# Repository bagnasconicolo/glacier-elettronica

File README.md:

# glacier-elettronica — Rivelatore di raggi cosmici

Front-end di lettura per un **rivelatore di muoni cosmici** basato su SiPM +
scintillatore: amplificatore veloce, discriminatore a soglia regolabile,
generazione del bias del SiPM, uscita TTL e **uscita 3,3 V per Raspberry Pi**.

Ricostruzione completa in KiCad — dal solo PDF scansionato dello schema originale
INFN sez. Torino ("Riv. Cosmici 2024 — Amplif, alim, soglie", S. Gallian) —
accompagnata da simulazioni circuitali non lineari, un verificatore che gira
**direttamente dallo schema**, la **simulazione LTspice della scheda completa** e un
sito didattico interattivo.

## Come funziona il circuito

Un muone attraversa lo scintillatore e produce un lampo di luce; il **SiPM**
(AFBR-S4N22P014M, polarizzato a ~38,4 V generati a bordo) lo converte in un
impulso di corrente. Due transistor — **BFR93A** (Q1) e **MMBTH81** (Q2) —
amplificano di ~28×. Il comparatore **MAX961** confronta con la soglia impostata
dal trimmer V2 e produce l'impulso digitale **CMP_Q**; una rete C9/R16 (latch)
evita i doppi conteggi. Da qui il segnale va al driver **MCP1402** (uscita TTL su
J2) e al buffer **74LVC1G17** alimentato a 3,3 V, che lo porta sul connettore
LEMO/J4 a 0–3,3 V, pronto per un GPIO del **Raspberry Pi**. Un timer **555** accende un LED per
11 ms a ogni evento.

Rate reale su una paletta 10×10 cm a livello del mare: **~1,7 muoni/s**.

| Schema | PCB |
|---|---|
|  |  |

## Struttura del repository

```
hardware/          progetto KiCad (schema, PCB, librerie, Gerber, BOM)
  riv_cosmici.kicad_pro/.kicad_sch/.kicad_pcb
  riv.kicad_sym, rivlib.pretty/        librerie simboli e footprint del progetto
  gerber/, riv_cosmici_gerber.zip      Gerber RS-274X + Excellon (pronti per il fab)
  bom/                                 distinta base (.xlsx e .csv) con codici Farnell/RS
  PRIMA_DI_ORDINARE.md                 cosa e' verificato e cosa decidere prima dell'ordine
  jlcpcb/                              Gerber, BOM e CPL per PCB + montaggio su JLCPCB
  variante_3ch/                        VARIANTE A 3 CANALI + coincidenza AND, uscite LEMO
  alpha_bpw21/                         mini-rivelatore di ALPHA con fotodiodo BPW21 (1 op-amp + Arduino)
  render3d/                            render 3D delle schede montate (three.js)
  previews/                            anteprime PNG
  generator/                           script Python che GENERANO lo hardware (sorgente)
simulation/        modelli circuitali non lineari + verifica dallo schema
  ltspice/             SCHEDA COMPLETA per LTspice (.asc) e ngspice (.cir) + verifica
  sim_catena.py        catena di segnale (SiPM -> ampli -> comparatore)
  sim_muoni.py         treno di muoni (Poisson + Landau) + dark count
  sim_buffer.py        (variante superata) vecchio buffer a 2 transistor
  sim_treno_completo.py (variante superata) catena fino a un Arduino a 5 V
  netlist_from_kicad.py   estrae la netlist dal .kicad_sch
  verify_from_schematic.py simula DALLA netlist estratta (front-end + uscita)
  make_recap.py        genera il PDF di recap
  riv_cosmici_frontend.cir  netlist SPICE del solo front-end (storica)
  figures/             grafici generati
web/               sito didattico interattivo (single-file, offline)
firmware/          (variante superata) sketch Arduino
docs/              schemi in PDF (1 e 3 canali), RECAP_progetto.pdf, schema_originale_INFN.pdf
```

## Due versioni

| | Scheda a 1 canale | Variante a 3 canali |
|---|---|---|
| Dove | `hardware/` | `hardware/variante_3ch/` |
| Barre / SiPM | 1 | 3 (bias e soglia regolabili per canale) |
| Uscite | LEMO/header 3,3 V + TTL 5 V | 3 LEMO 00 (canali) + 1 LEMO 00 (AND) |
| Coincidenza | — | 74LVC1G11 con jumper di esclusione |
| Test point | — | 6 per canale + 6 comuni |
| PCB | 80 × 55 mm | 103 × 215 mm, serigrafia didattica, 8 fori M3 |
| Schema PDF | `docs/schema_riv_cosmici_1canale.pdf` | `docs/schema_riv_cosmici_3canali.pdf` |

Render 3D delle schede montate: `hardware/render3d/out/1ch/` e `out/3ch/`
(rigenerabili con `python scene.py 3ch && node shoot.mjs 3ch`).

## Hardware (KiCad)

Apri `hardware/riv_cosmici.kicad_pro` con **KiCad 6 o successivo**. Le librerie di
progetto (`riv.kicad_sym`, `rivlib.pretty`) sono già referenziate da `sym-lib-table`
e `fp-lib-table` con percorso `${KIPRJMOD}`. I Gerber in `hardware/gerber/` sono
pronti per la produzione (2 layer, 80×55 mm; DRC geometrico e connettività a zero
errori). La BOM in `hardware/bom/` riporta i codici d'ordine Farnell/RS trascritti
dal progetto originale.

### Prima di ordinare

Leggi **[`hardware/PRIMA_DI_ORDINARE.md`](hardware/PRIMA_DI_ORDINARE.md)**: elenca cosa è
stato verificato (schema = originale INFN pin per pin, piedinature sui datasheet, DRC e
connettività del PCB, simulazione della scheda intera) e i punti da decidere al
montaggio, che non richiedono modifiche al PCB: R3 per restare sotto i 40 V del
LT3461, i condensatori d'uscita dei regolatori, l'ingombro di L1 e il LEMO.

Rigenerare tutto (schema, PCB, Gerber, BOM, anteprime) dal modello dati:

```bash
cd hardware/generator
python gen_sch.py && python gen_pcb.py && python gerber_out.py && python gen_bom.py
python gen_jlcpcb.py   # dopo aver aggiornato hardware/gerber e lo zip
python render_sch.py && python render_pcb.py
# schema, PCB e Gerber escono in generator/riv_cosmici/: copiarli in hardware/
```

## Simulazioni

Tutto in Python puro (nessun SPICE richiesto): un solver MNA + Newton con transistor
Ebers-Moll. Installa le dipendenze e lancia gli script da `simulation/`:

```bash
pip install -r requirements.txt
cd simulation
python sim_catena.py          # risposta della catena, punto di lavoro DC
python sim_muoni.py           # treno di muoni + dark count, reiezione
python sim_buffer.py          # buffer: CMP_Q vs TTL, storage time
python sim_treno_completo.py  # end-to-end fino al pin Arduino
```

Risultati principali (dettaglio in `simulation/RISULTATI_SIMULAZIONE.md`):
guadagno ~35 mV/fotoelettrone, saturazione oltre ~40 p.e.; soglia regolabile da
~2 mV a ~1,3 V; 7 muoni → 7 conteggi con 46 dark count rigettati; rate medio
1,68 conteggi/s a scala reale.

### Simulazione LTspice della scheda COMPLETA

In `simulation/ltspice/` c'è tutta la scheda — alimentazioni, boost 40 V, bias del SiPM,
front-end, soglia, comparatore con latch, driver TTL, 555 + LED, uscita per il
Raspberry Pi — come **schema LTspice** (`riv_cosmici_completo.asc`, si apre e si preme
Run) e come netlist (`.cir`, anche per ngspice). È generata dallo stesso modello dati
dello schema KiCad: riferimenti e nomi delle reti coincidono.

```bash
cd simulation/ltspice
python verifica_ltspice.py   # .asc == .cir, copertura KiCad, 21 controlli, grafico
```

Dettagli, parametri e limiti dei modelli: [`simulation/ltspice/LEGGIMI.md`](simulation/ltspice/LEGGIMI.md).

### Verifica DIRETTA dallo schema

Le simulazioni normali usano una netlist trascritta a mano. Per legare la verifica
allo schema vero:

```bash
cd simulation
python verify_from_schematic.py            # front-end letto dal .kicad_sch
python verify_from_schematic.py --uscita   # + stadio d'uscita (U9 -> J4) dal .kicad_sch
```

`netlist_from_kicad.py` estrae la netlist per geometria direttamente dal file
`hardware/riv_cosmici.kicad_sch` (valori, fili, etichette, alimentazioni) e
`verify_from_schematic.py` la simula: il punto di lavoro coincide col riferimento al
millivolt, e un errore introdotto nello schema (valore o cablaggio) cambia il
risultato — così la simulazione diventa una vera verifica dello schema.

Il **PDF di recap** con tutti i grafici e i numeri si rigenera con:
`python make_recap.py` → `docs/RECAP_progetto.pdf`.

## Sito didattico

In `web/` ci sono pagine HTML autonome (funzionano offline, senza librerie
esterne), con dentro lo **stesso solver circuitale** portato in JavaScript:

- `schematico_interattivo.html` — lo schema elettrico "vivo": lancia un muone al
  rallentatore, sonde sui nodi, componenti cliccabili, trimmer della soglia
  trascinabile, oscilloscopio.
- `viaggio_del_muone.html` — la catena stadio per stadio, con i grafici ricalcolati
  in tempo reale.
- `rivelatore_cosmici.html` — cruscotto con muoni animati e conteggio.

## Lettura con Raspberry Pi

J4 pin 1 → un GPIO (es. GPIO17) con 330 Ω in serie, J4 pin 2 → GND. L'uscita è
0–3,3 V. Ogni muone dà un impulso di ≥ 84 ns: va contato **a interrupt sul fronte di
salita** (es. `libgpiod`, eventi `RISING_EDGE`), non in polling. **Non collegare J2**
(TTL a 5 V) al Pi. Lo sketch in `firmware/` è della vecchia variante Arduino a 5 V.

## Rigenerare lo hardware

Gli script in `hardware/generator/` sono il "sorgente" da cui sono stati generati
schema, PCB, Gerber e BOM (via codice, per costruzione riproducibile), tutti dallo
stesso modello dati `netdata.py`; i comandi sono nella sezione "Prima di ordinare".
Anche la simulazione LTspice (`simulation/ltspice/gen_ltspice.py`) parte da lì.

## Crediti e licenza

Progetto originale: **INFN sezione di Torino**, "Riv. Cosmici 2024 — Amplif, alim,
soglie" (S. Gallian, 2024). Ricostruzione KiCad, buffer, simulazioni, verifica e
materiale didattico: questo repository.

Rilasciato sotto **CERN Open Hardware Licence Version 2 — Weakly Reciprocal**
(CERN-OHL-W-2.0): vedi `LICENSE` e `LICENSE.CERN-OHL-W-2.0.txt`. Il software di
supporto (script Python/JS, firmware) è distribuito con lo stesso spirito.

## Monitor delle tensioni (scheda a 3 canali)

Un ADC MCP3424 sulla scheda legge i tre bias dei SiPM e l'alta tensione; il Raspberry Pi li legge in I²C con `software/monitor_tensioni.py`. Dettagli e verifica che non disturbi le misure: `hardware/variante_3ch/LEGGIMI.md` e `simulation/ltspice/verifica_monitor.py`.

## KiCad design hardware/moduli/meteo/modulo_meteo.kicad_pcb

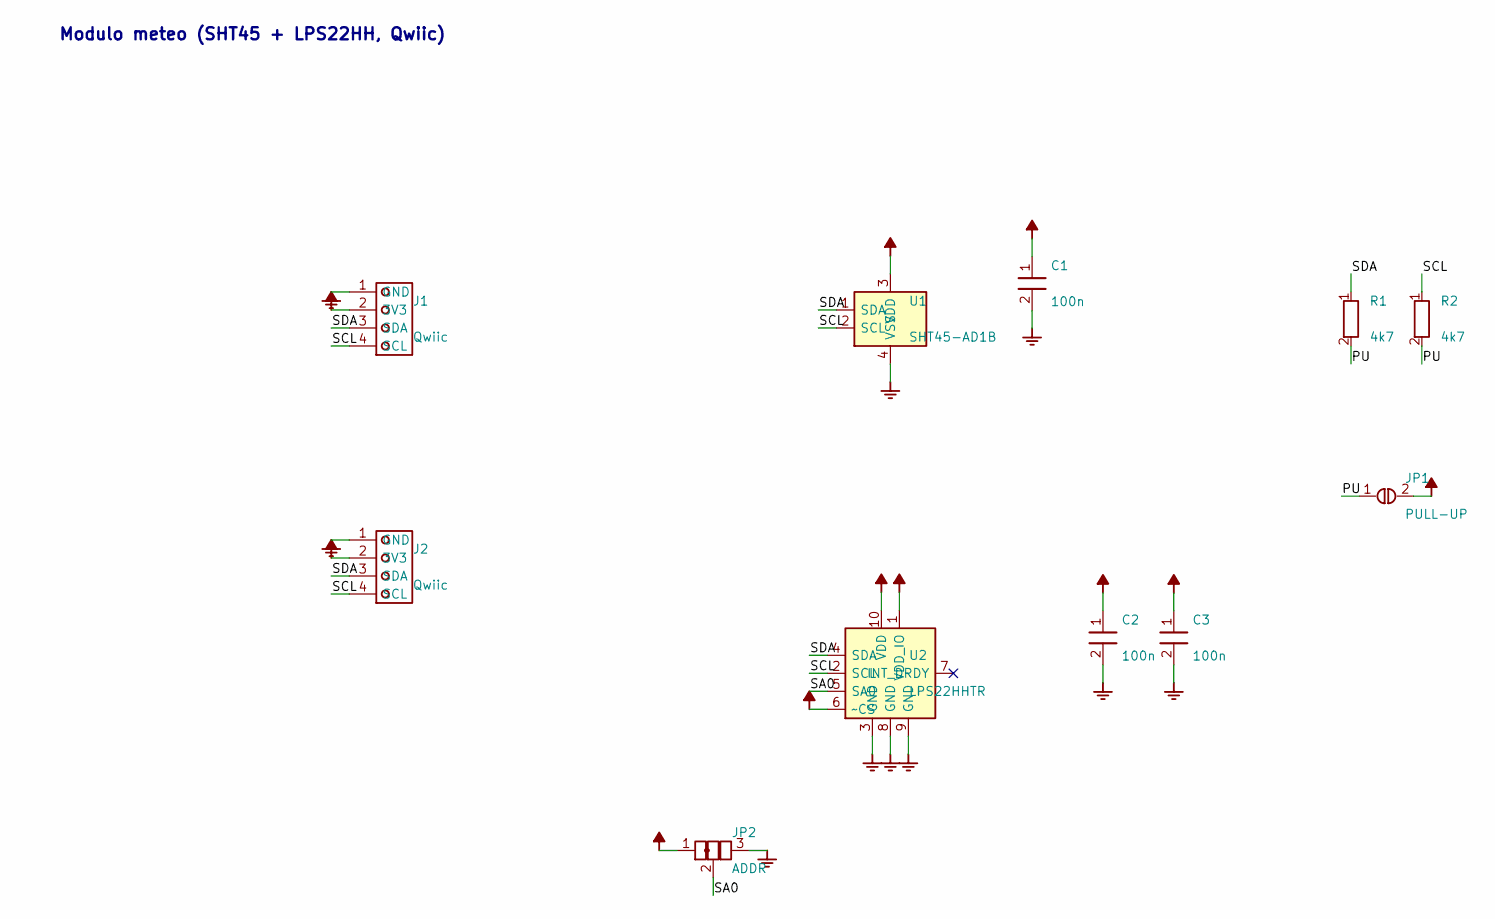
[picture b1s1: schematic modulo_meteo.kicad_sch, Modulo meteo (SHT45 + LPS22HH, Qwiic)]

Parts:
C1, C2, C3: 100n; C_0603_1608Metric
J1, J2: Qwiic; JST_SH_SM04B-SRSS-TB_1x04-1MP_P1.00mm_Horizontal
JP1: PULL-UP; SolderJumper-2_P1.3mm_Open_RoundedPad1.0x1.5mm
JP2: ADDR; SolderJumper-3_P1.3mm_Bridged12_RoundedPad1.0x1.5mm
R1, R2: 4k7; R_0603_1608Metric
U1: SHT45-AD1B; Sensirion_DFN-4_1.5x1.5mm_P0.8mm_SHT4x_KeepoutCentro
U2: LPS22HHTR; ST_HLGA-10_2x2mm_P0.5mm_LayoutBorder3x2y

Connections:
+3V3: C1.1, C2.1, C3.1, J1.2 (3V3), J2.2 (3V3), JP1.2, JP2.1, U1.3 (VDD), U2.1 (VDD_IO), U2.6 (~CS), U2.10 (VDD)
GND: C1.2, C2.2, C3.2, J1.1 (GND), J2.1 (GND), JP2.3, U1.4 (VSS), U2.3 (GND), U2.8 (GND), U2.9 (GND)
PU: JP1.1, R1.2, R2.2
SA0: JP2.2, U2.5 (SA0)
SCL: J1.4 (SCL), J2.4 (SCL), R2.1, U1.2 (SCL), U2.2 (SCL)
SDA: J1.3 (SDA), J2.3 (SDA), R1.1, U1.1 (SDA), U2.4 (SDA)

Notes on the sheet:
Modulo meteo (SHT45 + LPS22HH, Qwiic)

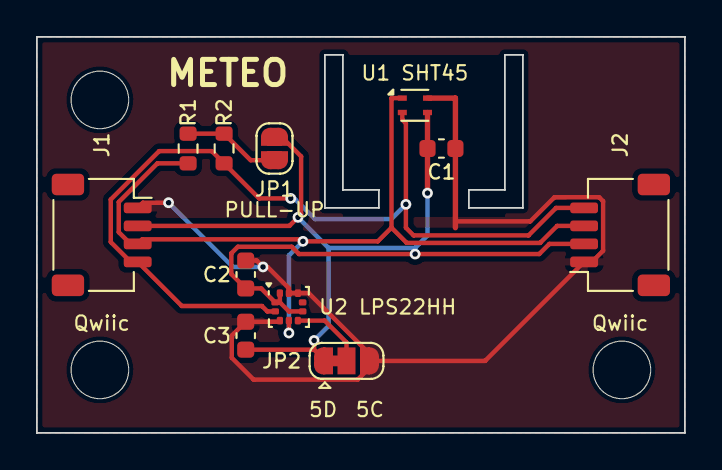
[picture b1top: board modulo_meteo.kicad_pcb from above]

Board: 2 copper layers, 36.0 x 22.0 mm, 14 parts (0 on the bottom side), 6 nets.

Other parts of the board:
H1, H2, H3: M3; MountingHole_3.2mm_M3

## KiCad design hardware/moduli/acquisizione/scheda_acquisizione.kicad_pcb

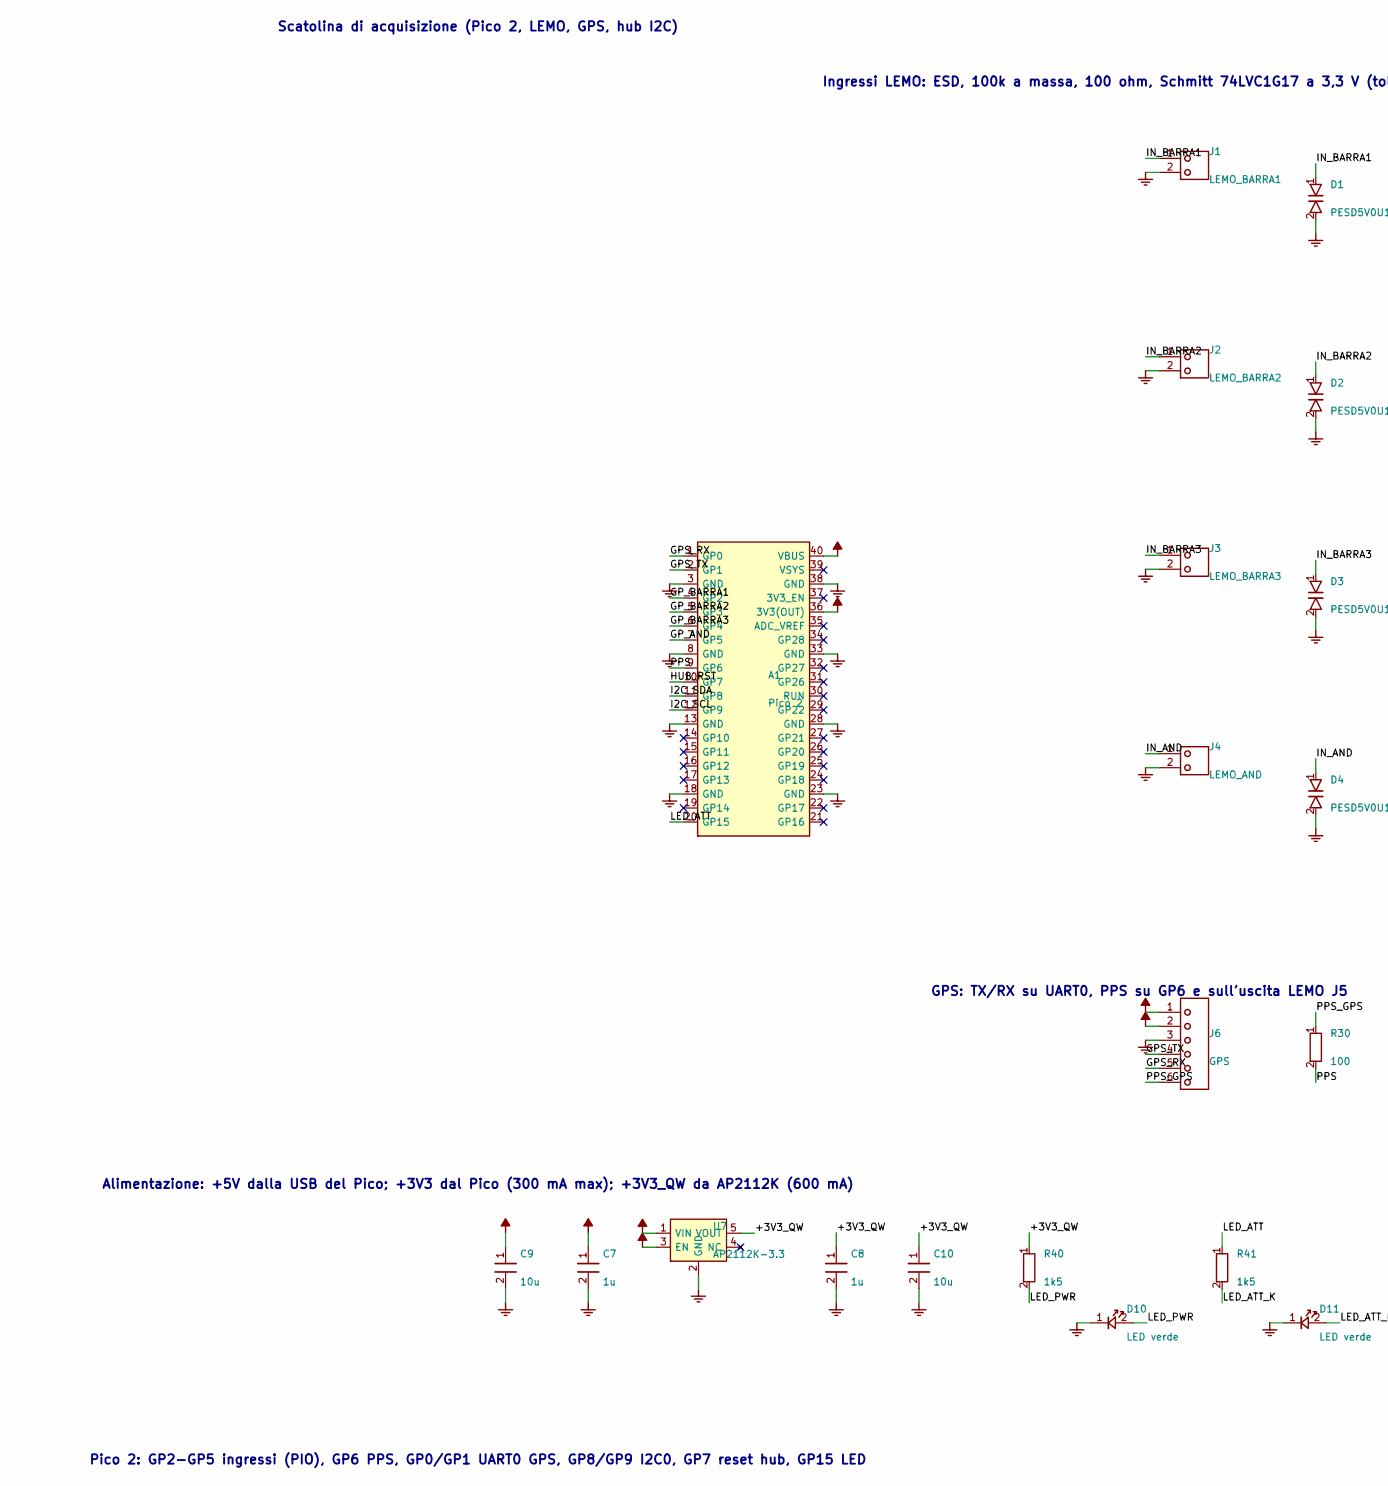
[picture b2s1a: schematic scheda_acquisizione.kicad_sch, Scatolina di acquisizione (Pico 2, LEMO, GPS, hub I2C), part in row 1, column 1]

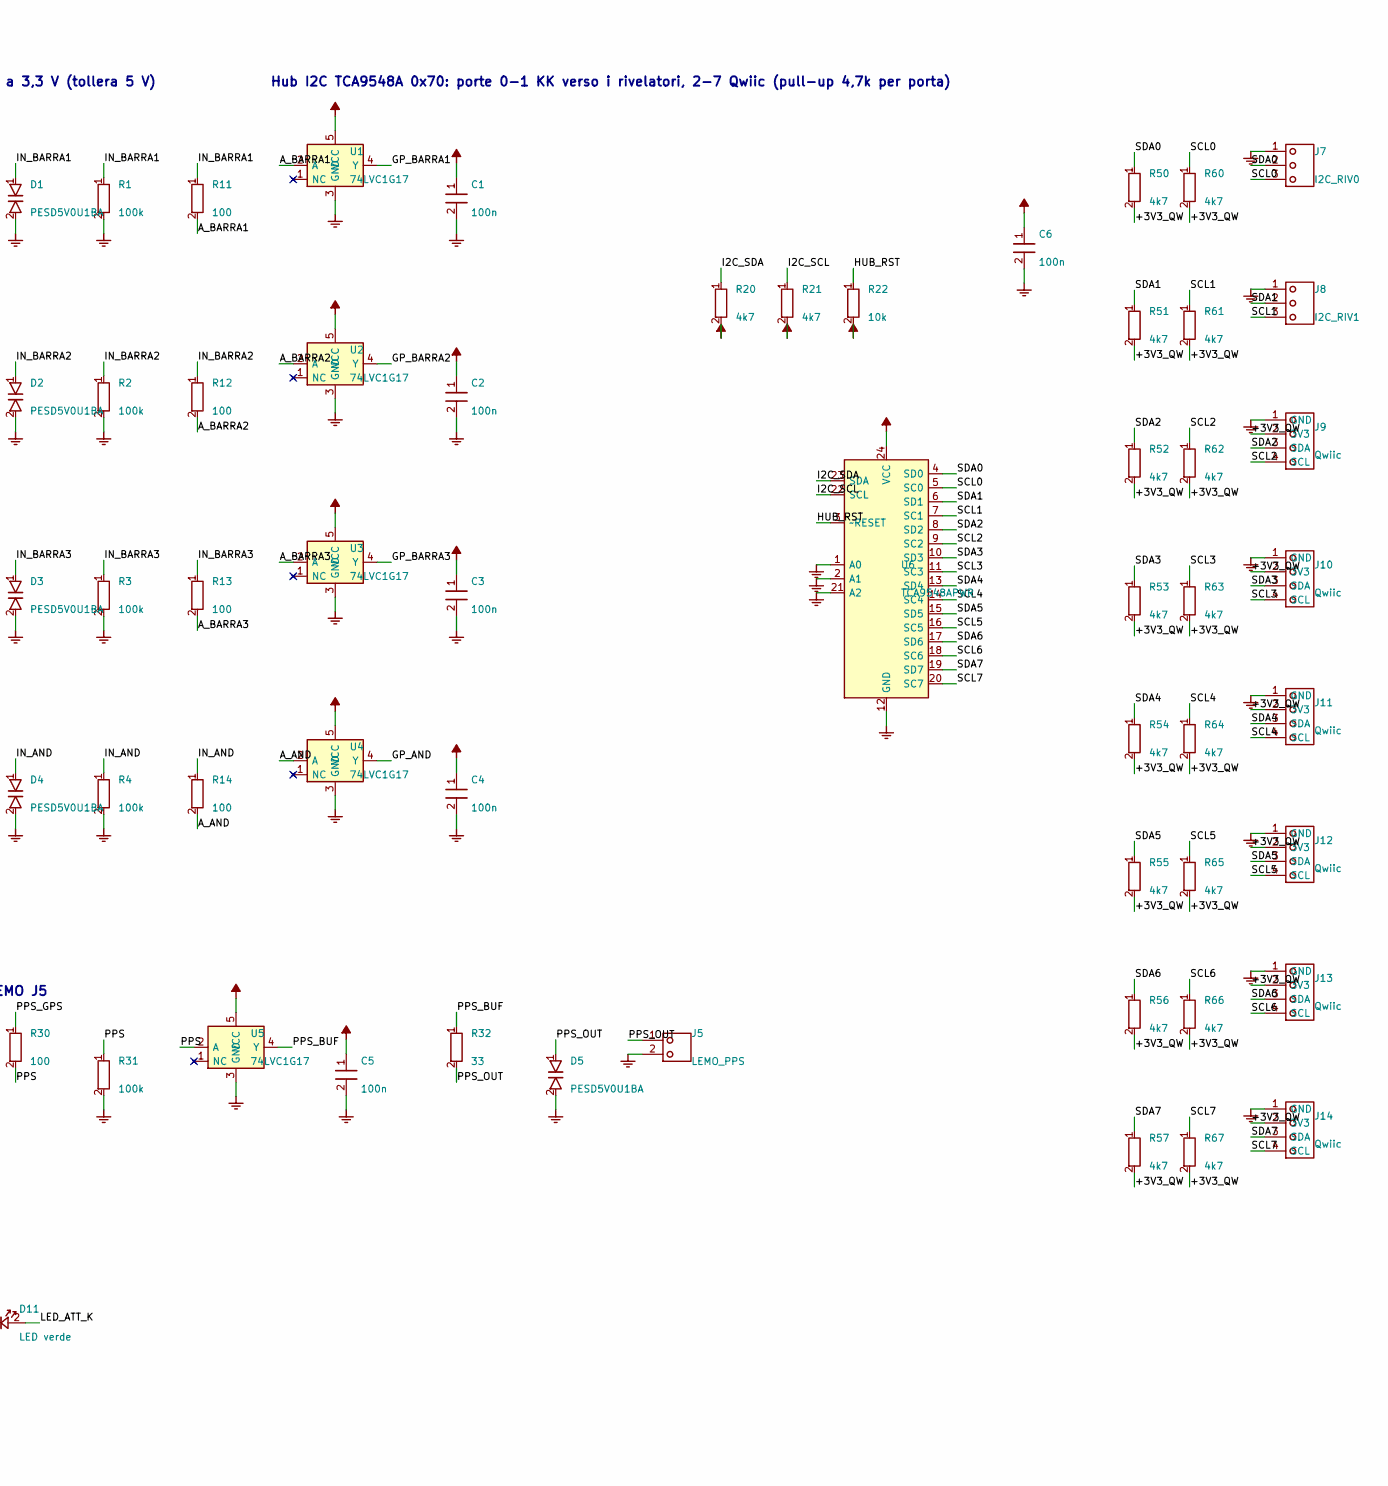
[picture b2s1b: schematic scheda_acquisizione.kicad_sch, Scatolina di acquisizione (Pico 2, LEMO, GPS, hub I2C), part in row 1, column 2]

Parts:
A1: Pico 2; RPi_Pico2_Socket
C1, C2, C3, C4, C5, C6: 100n; C_0603_1608Metric
C7, C8: 1u; C_0603_1608Metric
C9, C10: 10u; C_1206_3216Metric
D1, D2, D3, D4, D5: PESD5V0U1BA; D_SOD-323
D10, D11: LED verde; LED_0805_2012Metric
J1: LEMO_BARRA1; LEMO_EPL00
J2: LEMO_BARRA2; LEMO_EPL00
J3: LEMO_BARRA3; LEMO_EPL00
J4: LEMO_AND; LEMO_EPL00
J5: LEMO_PPS; LEMO_EPL00
J6: GPS; PinHeader_1x06_P2.54mm_Vertical
J7: I2C_RIV0; Molex_KK-254_AE-6410-03A_1x03_P2.54mm_Vertical
J8: I2C_RIV1; Molex_KK-254_AE-6410-03A_1x03_P2.54mm_Vertical
J9, J10, J11, J12, J13, J14: Qwiic; JST_SH_SM04B-SRSS-TB_1x04-1MP_P1.00mm_Horizontal
R1, R2, R3, R4, R31: 100k; R_0603_1608Metric
R11, R12, R13, R14, R30: 100; R_0603_1608Metric
R20, R21, R50, R51, R52, R53, R54, R55, R56, R57, R60, R61, R62, R63, R64, R65, R66, R67: 4k7; R_0603_1608Metric
R22: 10k; R_0603_1608Metric
R32: 33; R_0603_1608Metric
R40, R41: 1k5; R_0603_1608Metric
U1, U2, U3, U4, U5: 74LVC1G17; SOT-23-5
U6: TCA9548APWR; TSSOP-24_4.4x7.8mm_P0.65mm
U7: AP2112K-3.3; SOT-23-5

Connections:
+3V3: A1.36 (3V3(OUT)), C1.1, C2.1, C3.1, C4.1, C5.1, C6.1, J6.2, R20.2, R21.2, R22.2, U1.5 (VCC), U2.5 (VCC), U3.5 (VCC), U4.5 (VCC), U5.5 (VCC), U6.24 (VCC)
+3V3_QW: C8.1, C10.1, J9.2 (3V3), J10.2 (3V3), J11.2 (3V3), J12.2 (3V3), J13.2 (3V3), J14.2 (3V3), R40.1, R50.2, R51.2, R52.2, R53.2, R54.2, R55.2, R56.2, R57.2, R60.2, R61.2, R62.2, R63.2, R64.2, R65.2, R66.2, R67.2, U7.5 (VOUT)
+5V: A1.40 (VBUS), C7.1, C9.1, J6.1, U7.1 (VIN), U7.3 (EN)
A_AND: R14.2, U4.2 (A)
A_BARRA1: R11.2, U1.2 (A)
A_BARRA2: R12.2, U2.2 (A)
A_BARRA3: R13.2, U3.2 (A)
GND: A1.3 (GND), A1.8 (GND), A1.13 (GND), A1.18 (GND), A1.23 (GND), A1.28 (GND), A1.33 (GND), A1.38 (GND), C1.2, C2.2, C3.2, C4.2, C5.2, C6.2, C7.2, C8.2, C9.2, C10.2, D1.2, D2.2, D3.2, D4.2, D5.2, D10.1 (K), D11.1 (K), J1.2, J2.2, J3.2, J4.2, J5.2, J6.3, J7.1, J8.1, J9.1 (GND), J10.1 (GND), J11.1 (GND), J12.1 (GND), J13.1 (GND), J14.1 (GND), R1.2, R2.2, R3.2, R4.2, R31.2, U1.3 (GND), U2.3 (GND), U3.3 (GND), U4.3 (GND), U5.3 (GND), U6.1 (A0), U6.2 (A1), U6.12 (GND), U6.21 (A2), U7.2 (GND)
GPS_RX: A1.1 (GP0), J6.5
GPS_TX: A1.2 (GP1), J6.4
GP_AND: A1.7 (GP5), U4.4 (Y)
GP_BARRA1: A1.4 (GP2), U1.4 (Y)
GP_BARRA2: A1.5 (GP3), U2.4 (Y)
GP_BARRA3: A1.6 (GP4), U3.4 (Y)
HUB_RST: A1.10 (GP7), R22.1, U6.3 (~RESET)
I2C_SCL: A1.12 (GP9), R21.1, U6.22 (SCL)
I2C_SDA: A1.11 (GP8), R20.1, U6.23 (SDA)
IN_AND: D4.1, J4.1, R4.1, R14.1
IN_BARRA1: D1.1, J1.1, R1.1, R11.1
IN_BARRA2: D2.1, J2.1, R2.1, R12.1
IN_BARRA3: D3.1, J3.1, R3.1, R13.1
LED_ATT: A1.20 (GP15), R41.1
LED_ATT_K: D11.2 (A), R41.2
LED_PWR: D10.2 (A), R40.2
PPS: A1.9 (GP6), R30.2, R31.1, U5.2 (A)
PPS_BUF: R32.1, U5.4 (Y)
PPS_GPS: J6.6, R30.1
PPS_OUT: D5.1, J5.1, R32.2
SCL0: J7.3, R60.1, U6.5 (SC0)
SCL1: J8.3, R61.1, U6.7 (SC1)
SCL2: J9.4 (SCL), R62.1, U6.9 (SC2)
SCL3: J10.4 (SCL), R63.1, U6.11 (SC3)
SCL4: J11.4 (SCL), R64.1, U6.14 (SC4)
SCL5: J12.4 (SCL), R65.1, U6.16 (SC5)
SCL6: J13.4 (SCL), R66.1, U6.18 (SC6)
SCL7: J14.4 (SCL), R67.1, U6.20 (SC7)
SDA0: J7.2, R50.1, U6.4 (SD0)
SDA1: J8.2, R51.1, U6.6 (SD1)
SDA2: J9.3 (SDA), R52.1, U6.8 (SD2)
SDA3: J10.3 (SDA), R53.1, U6.10 (SD3)
SDA4: J11.3 (SDA), R54.1, U6.13 (SD4)
SDA5: J12.3 (SDA), R55.1, U6.15 (SD5)
SDA6: J13.3 (SDA), R56.1, U6.17 (SD6)
SDA7: J14.3 (SDA), R57.1, U6.19 (SD7)

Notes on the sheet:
Pico 2: GP2-GP5 ingressi (PIO), GP6 PPS, GP0/GP1 UART0 GPS, GP8/GP9 I2C0, GP7 reset hub, GP15 LED
Ingressi LEMO: ESD, 100k a massa, 100 ohm, Schmitt 74LVC1G17 a 3,3 V (tollera 5 V)
Hub I2C TCA9548A 0x70: porte 0-1 KK verso i rivelatori, 2-7 Qwiic (pull-up 4,7k per porta)
GPS: TX/RX su UART0, PPS su GP6 e sull'uscita LEMO J5
Alimentazione: +5V dalla USB del Pico; +3V3 dal Pico (300 mA max); +3V3_QW da AP2112K (600 mA)
Scatolina di acquisizione (Pico 2, LEMO, GPS, hub I2C)

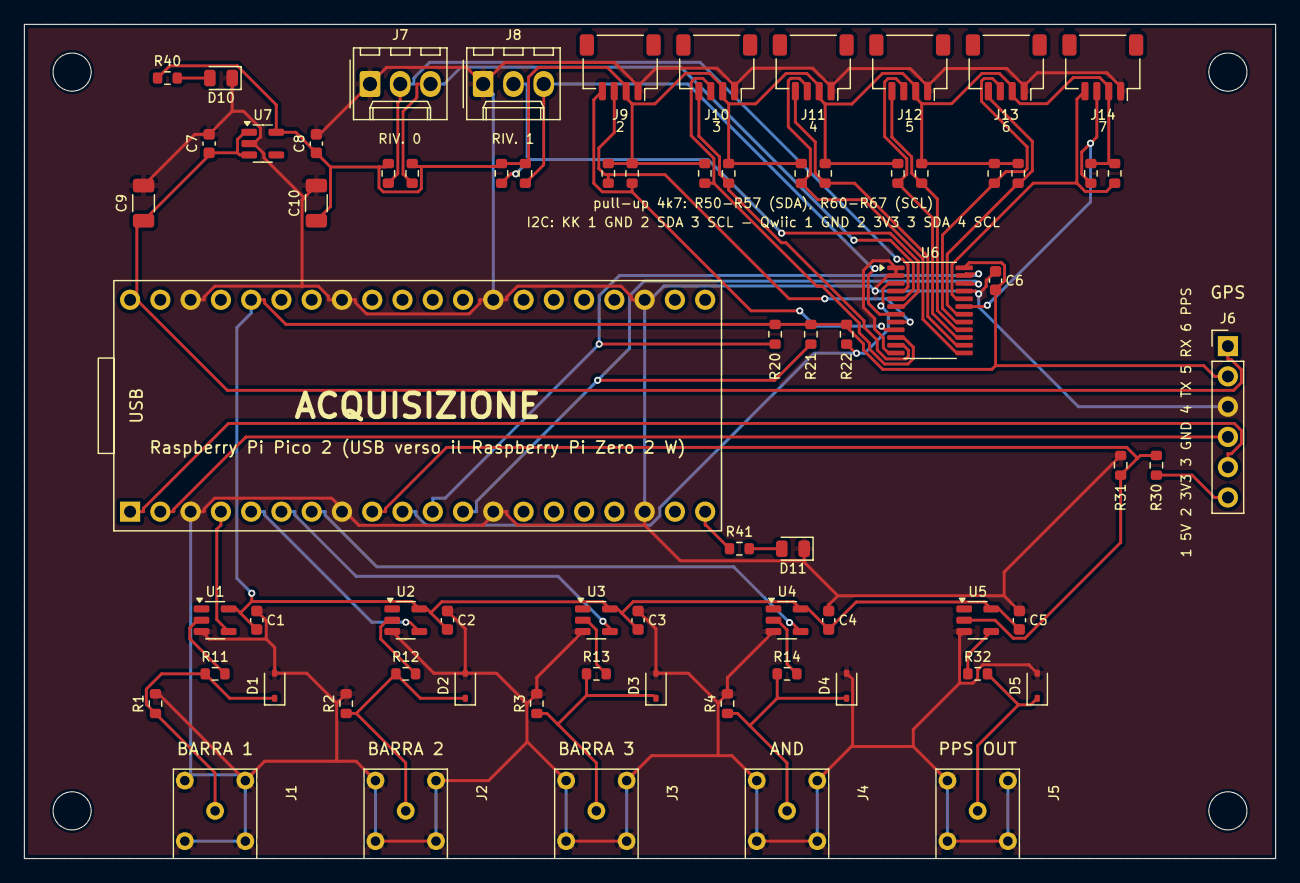
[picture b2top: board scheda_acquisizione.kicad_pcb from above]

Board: 2 copper layers, 105.0 x 70.0 mm, 75 parts (0 on the bottom side), 44 nets.

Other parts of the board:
H1, H2, H3, H4: M3; MountingHole_3.2mm_M3
